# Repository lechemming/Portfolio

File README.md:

# Portfolio
Portfolio for Lucas Hemming

I have been a student at Iowa State University for 3 years starting in fall of 2023, strong interest in systems design. Particular interest in VLSI/ASIC design, largely becuase it's a big intersection and involved many different modes and methods of design. Before that I transfered from Madison College in Madison, Wisconsin where I went for around 2 years. I think of myself as an engineer who wants to be very familiary with every level and layer in a system, and because systems these days are so complex this is a challenge. The upper level courses I took at Iowa State reflect that. I took higher level courses in Analog VLSI, Highspeed Systems(RF), Machine Learning(signal processing and computer vision), and Computer Architecture. This is a fairly odd spread of courses, but I found that it gave me a very strong foundation in many layers that are fundamental to electrical engineering. I find that projects are the best ways to explore a topic and at ISU I had many opportunities in classes to have fairly free reign to explore a project and do with it whatever I wished. I think this free formed approach to a lot of the given projects inspired me to continue on with some personal projects, and gave me confidence in my ability as an engineer, while also somewhat tempering myself with the difficulty involved in continuing a project until supposed completion.

Outside of class project's I am a dad and have been for the whole time I was at ISU, I would be lying if I said balancing home life with my partner and son didn't contribute some unique challenges to life at Iowa State, but all in all professors and classmates were always understanding and accomodating when they could be, and I never felt like I was not supported in my education. I also have always had an interest in game development and design, even if that isn't something I want to do professionally, as an Electrical Engineering student I had plenty of opportunities in class's and with fellow students to explore extracuricular interests. While in this portfolio I only shared a few project's that I have been involved in there had been plenty of other places where I as an engineer grew, and I will always look back on my time at ISU fondly as a place where I grew a lot.

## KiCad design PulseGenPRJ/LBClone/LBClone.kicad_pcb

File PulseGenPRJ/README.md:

# Sub Nanosecond pulse generator for TDR

This was a project for my high speed systems class, the project was very open ended and the choice to make
a pulse generator was a specificc choice of my own. It involved numerous hours of research, schematic building,
selecting components for my BOM, layout, and assembly. I took on the project alone and was able to explore
pcb design for a relatively high speed design and learn some of the nuances involved in that.

The project was designed using KiCAD and was fabricated by JLC PCB. This was only my second time doing a project like this to completion, and the first time doing it without a specific reference design that I was essentially copying. It was a good practical introduction into producing my own PCB's and making calls about how I should implement my design in a cost effective way while fitting my specification. It also required me to make my own and make modification to device footprints and read a lot about implementation of specific IC's within datasheets.

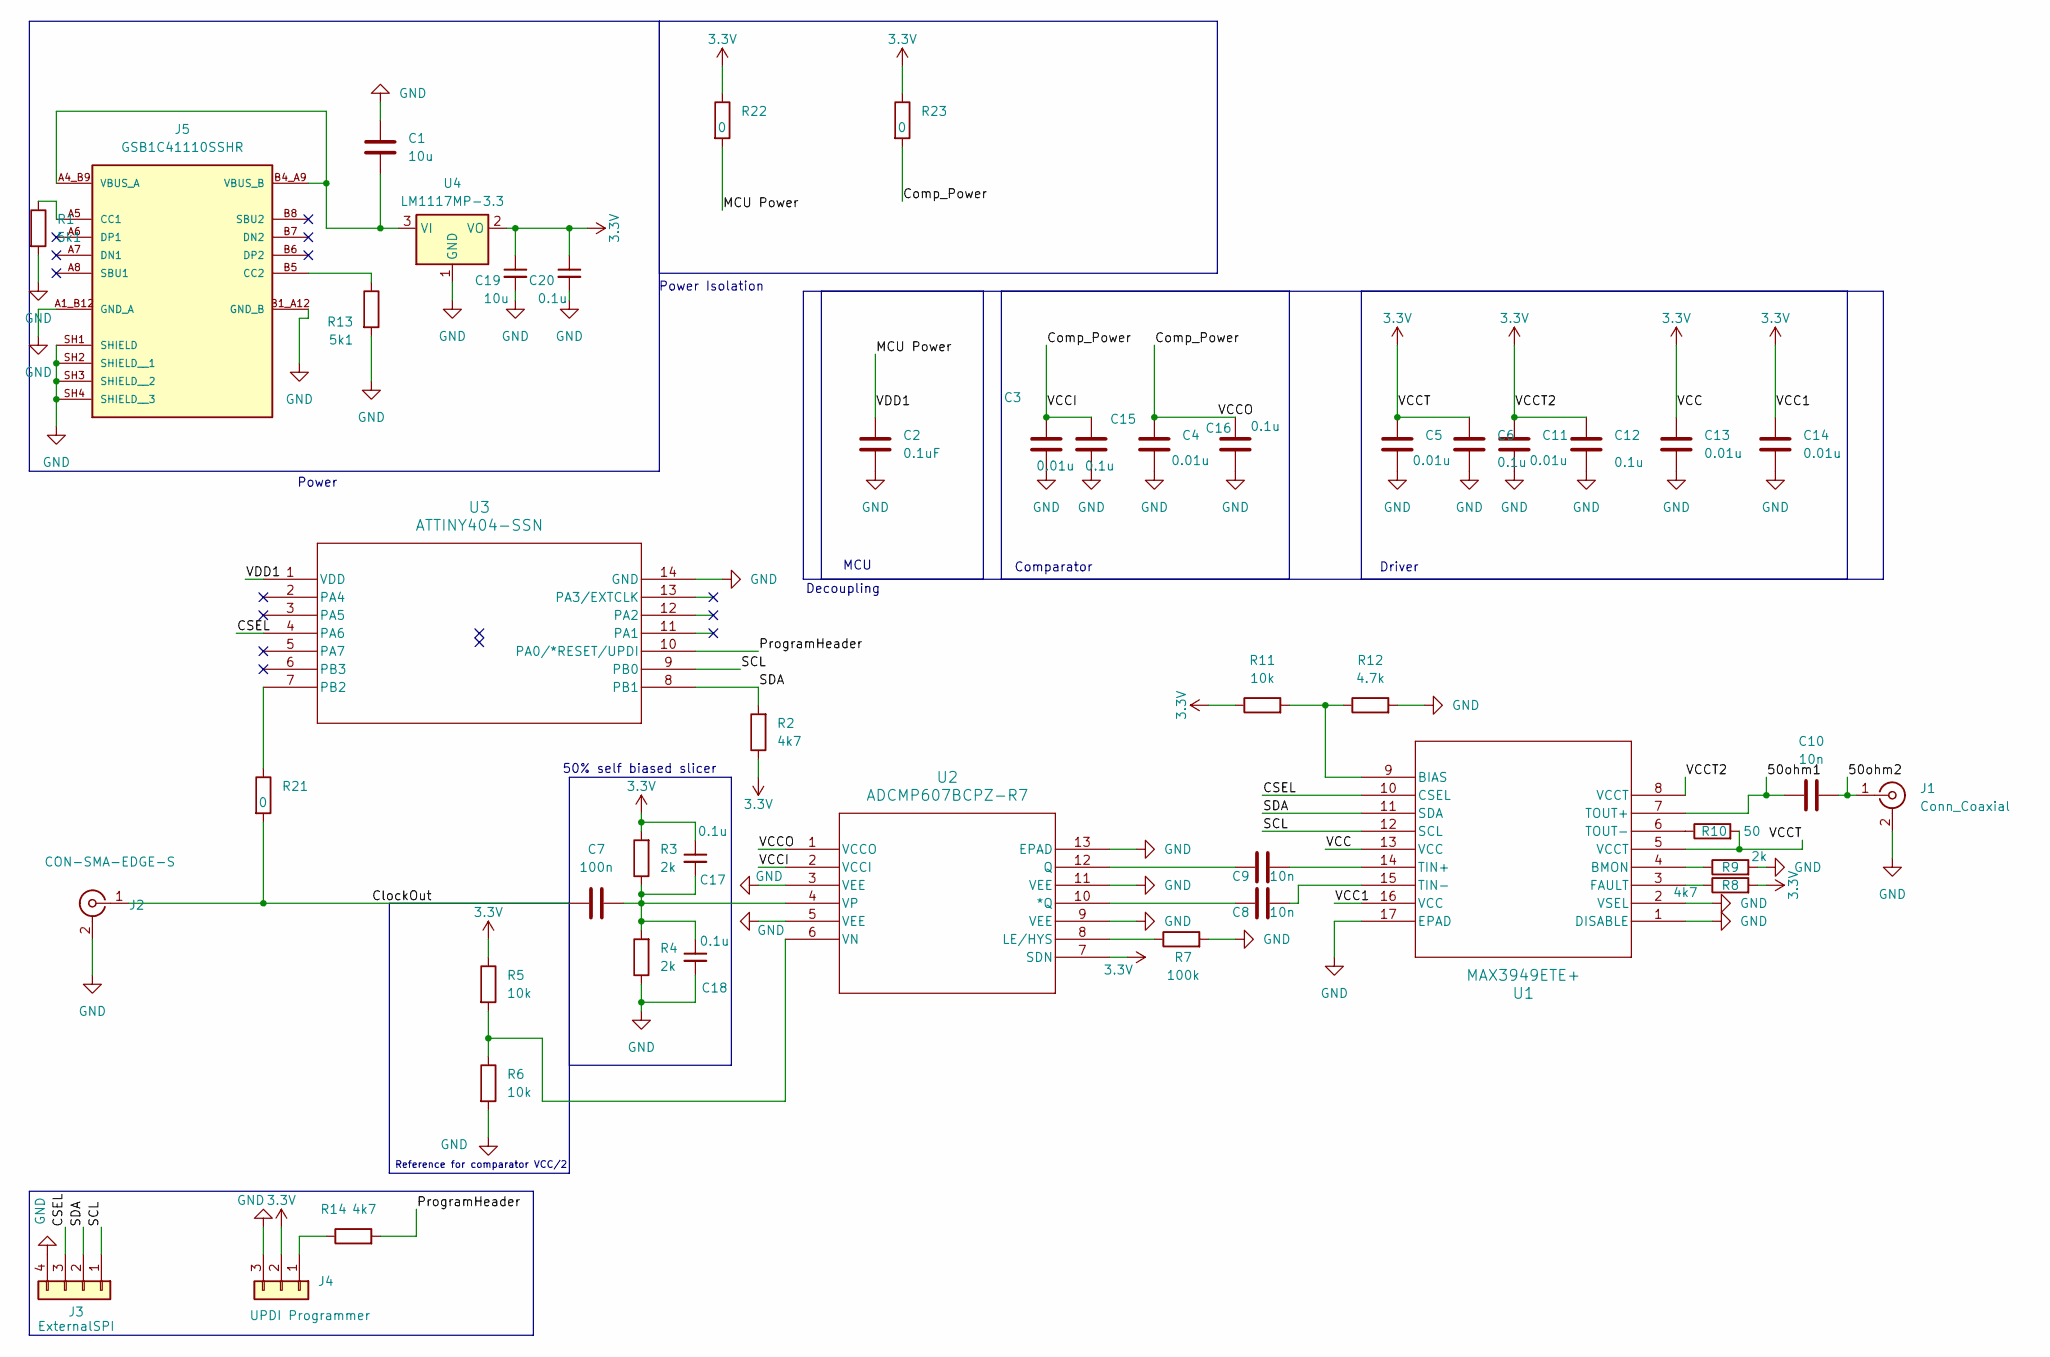
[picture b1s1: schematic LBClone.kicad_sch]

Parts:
C1: 10u; C_0805_2012Metric
C2: 0.1uF; C_0201_0603Metric
C3, C4, C5, C11, C13, C14: 0.01u; R_0402_1005Metric
C6: 0.1u; R_0402_1005Metric
C7: 100n; C_0201_0603Metric
C8, C9: 10n; R_0402_1005Metric
C10: 10n; C_0402_1005Metric
C12, C15, C16: 0.1u; C_0201_0603Metric
C17, C18, C20: 0.1u; C_0603_1608Metric; Voltage 1kV; Tolerance 100%
C19: 10u; C_0805_2012Metric; Voltage 1kV; Tolerance 100%
J1: Conn_Coaxial; 142-0741-851SMA
J2: CON-SMA-EDGE-S; RFSOLUTIONS_CON-SMA-EDGE-S; PARTREV 1
J3: ExternalSPI; PinHeader_1x04_P2.54mm_Vertical
J4: UPDI Programmer; PinHeader_1x03_P2.54mm_Vertical
J5: GSB1C41110SSHR; AMPHENOL_GSB1C41110SSHR; PARTREV AX1
R1, R13: 5k1; R_0603_1608Metric
R2, R8, R14: 4k7; R_0603_1608Metric
R3, R4, R9: 2k; R_0603_1608Metric
R5, R6: 10k; R_0603_1608Metric
R7: 100k; R_0603_1608Metric
R10: 50; R_0402_1005Metric
R11: 10k; R_0201_0603Metric
R12: 4.7k; R_0201_0603Metric
R21, R22, R23: 0; R_0603_1608Metric
U1: MAX3949ETE+; CP_16_3_ADI-L
U2: ADCMP607BCPZ-R7; CP_12_5_ADI-L
U3: ATTINY404-SSN; SOIC14_SL_MCH
U4: LM1117MP-3.3; SOT-223-3_TabPin2

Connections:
3.3V: C5.1, C6.1, C11.1, C12.1, C13.1, C14.1, C17.1, C19.1, C20.1, J4.2, R2.1, R3.2, R5.1, R8.2, R10.2, R11.1, R22.1, R23.1, U1.5 (VCCT), U1.8 (VCCT), U1.13 (VCC), U1.16 (VCC), U2.7 (SDN), U4.2 (VO); also elsewhere on the board
/50ohm1: C10.1, U1.7 (TOUT+)
/50ohm2: C10.2, J1.1 (In)
/CSEL: J3.3, U1.10 (CSEL), U3.4 (PA6)
/ClockOut: C7.1, J2.1 (In), R21.2
/Comp_Power: C3.1, C4.1, C15.1, C16.1, R23.2, U2.1 (VCCO), U2.2 (VCCI)
/MCU Power: C2.1, R22.2, U3.1 (VDD)
/ProgramHeader: R14.2, U3.10 (PA0/*RESET/UPDI)
/SCL: J3.1, U1.12 (SCL), U3.9 (PB0)
/SDA: J3.2, R2.2, U1.11 (SDA), U3.8 (PB1)
GND: C1.1, C2.2, C3.2, C4.2, C5.2, C6.2, C11.2, C12.2, C13.2, C14.2, C15.2, C16.2, C18.2, C19.2, C20.2, J1.2 (Ext), J2.2 (Ext), J3.4, J4.3, J5.A1_B12 (GND_A), J5.B1_A12 (GND_B), J5.SH1 (SHIELD), J5.SH2 (SHIELD__1), J5.SH3 (SHIELD__2), J5.SH4 (SHIELD__3), R1.2, R4.1, R6.2, R7.2, R9.2, R12.2, R13.2, U1.1 (DISABLE), U1.2 (VSEL), U1.17 (EPAD), U2.3 (VEE), U2.5 (VEE), U2.9 (VEE), U2.11 (VEE), U2.13 (EPAD), U3.14 (GND), U4.1 (GND); also elsewhere on the board
unnamed: J4.1, R14.1
unnamed: J5.A5 (CC1), R1.1
unnamed: J5.B5 (CC2), R13.1
unnamed: C1.2, J5.A4_B9 (VBUS_A), J5.B4_A9 (VBUS_B), U4.3 (VI)
unnamed: R11.2, R12.1, U1.9 (BIAS)
unnamed: R9.1, U1.4 (BMON)
unnamed: R8.1, U1.3 (FAULT)
unnamed: C9.2, U1.14 (TIN+)
unnamed: C8.2, U1.15 (TIN-)
unnamed: R10.1, U1.6 (TOUT-)
unnamed: C8.1, U2.10 (*Q)
unnamed: R7.1, U2.8 (LE/HYS)
unnamed: C9.1, U2.12 (Q)
unnamed: R5.2, R6.1, U2.6 (VN)
unnamed: C7.2, C17.2, C18.1, R3.1, R4.2, U2.4 (VP)
unnamed: R21.1, U3.7 (PB2)

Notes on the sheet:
50% self biased slicer
Comparator
Reference for comparator VCC/2
Driver
MCU
Power
Power Isolation
Decoupling

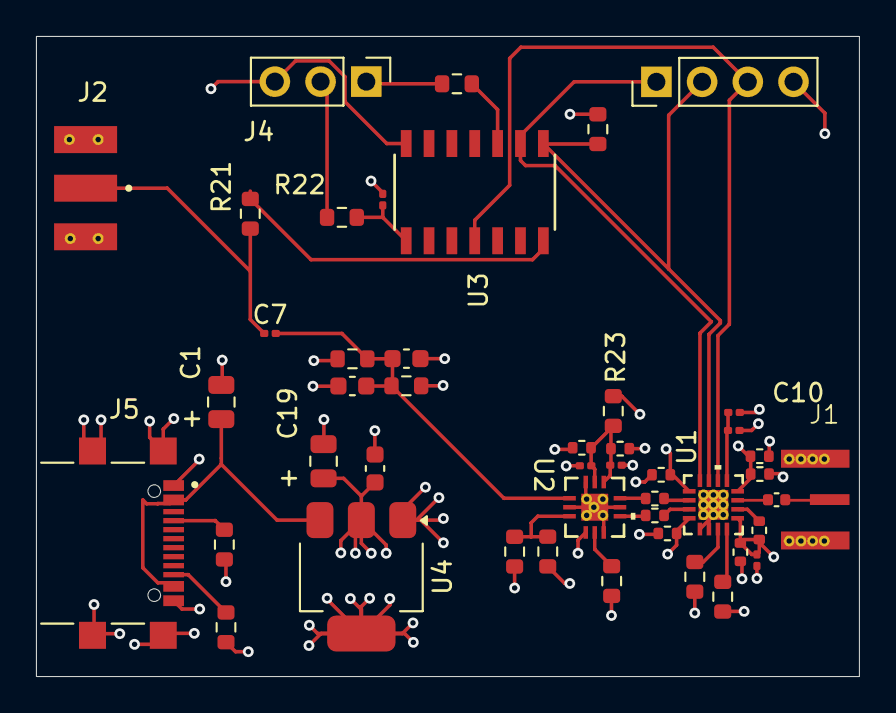
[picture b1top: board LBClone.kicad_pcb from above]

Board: 4 copper layers, 45.7 x 35.6 mm, 46 parts (0 on the bottom side), 27 nets.

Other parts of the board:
+  C19: 10u; C_0805_2012Metric

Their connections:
3.3V: + C19.1; also elsewhere on the board
GND: + C19.2; also elsewhere on the board

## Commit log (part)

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2026-06-23 Added PulseGen Project to portfolio
2026-06-23 finetuning/classification of tumors
2026-06-23 changed structure
2026-06-23 Merging stuctures
2026-06-23 Rename README.txt to README.md
